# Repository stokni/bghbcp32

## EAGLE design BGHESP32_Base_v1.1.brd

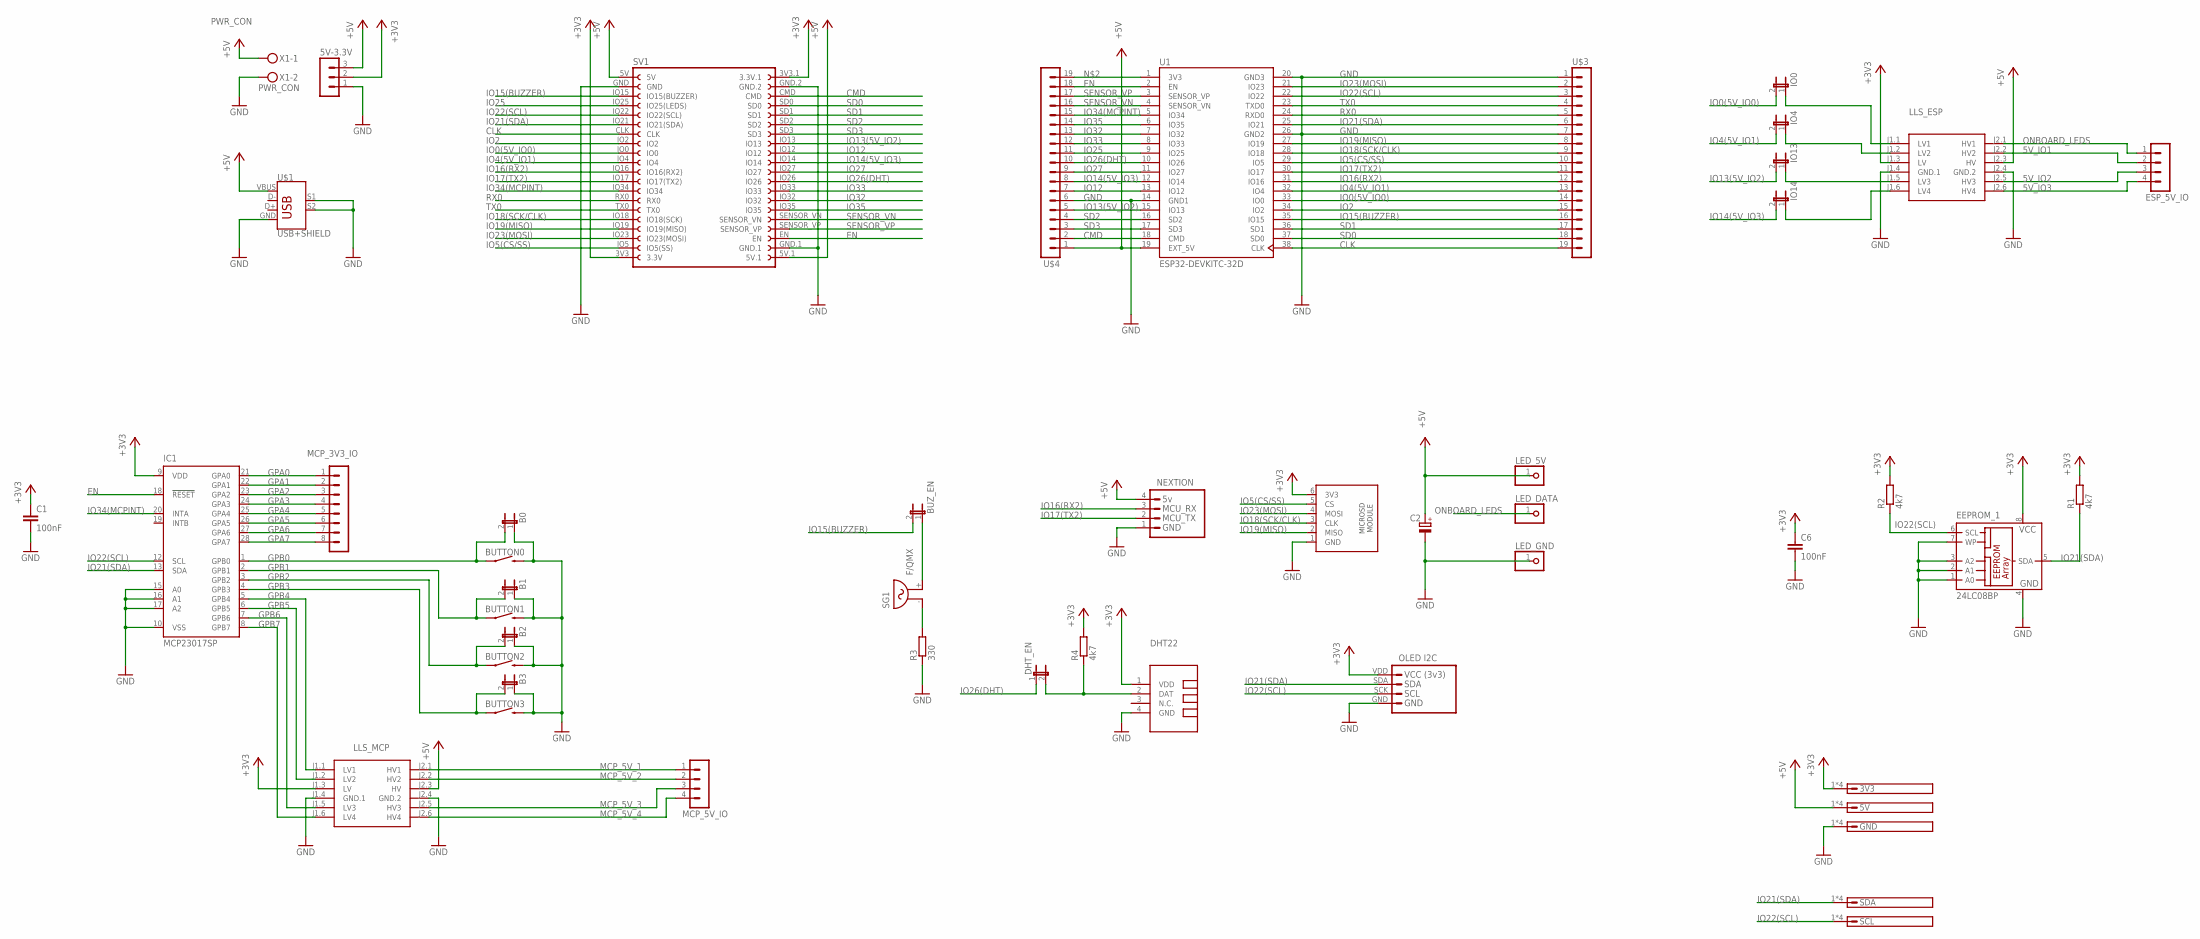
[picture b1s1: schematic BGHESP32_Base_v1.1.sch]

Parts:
3V3, 5V: IO-OUT-4PIO-OUT-4[; IO-OUT-4P
5V-3.3V: MA03-1
B0, B1, B2, B3: JP1E; JP1
BUTTON0, BUTTON1, BUTTON2, BUTTON3: MOMENTARY-SWITCH-SPST-PTH-6.0MM; TACTILE_SWITCH_PTH_6.0MM
BUZ_EN: JP1E; JP1
C1, C6: 100nF; C050-025X075
C2: CPOL-EUE5-10.5; E5-10,5
DHT22: TEMP-HUM-SENSOR-DHT22
DHT_EN: JP1E; JP1
EEPROM_1: 24LC08BP; DIL8
ESP_5V_IO: MA04-1
GND: IO-OUT-4PIO-OUT-4[; IO-OUT-4P
IC1: MCP23017SP; DIL28-3
IO0, IO4, IO13, IO14: JP1E; JP1
LED_5V: PINHD-1X1; 1X01
LED_DATA: PINHD-1X1; 1X01
LED_GND: PINHD-1X1; 1X01
LLS_ESP: LEVEL-SHIFTER-4CH
LLS_MCP: LEVEL-SHIFTER-4CH
MCP_3V3_IO: MA08-1
MCP_5V_IO: MA04-1
R1, R2, R4: 4k7; 0207/10
R3: 330; 0207/10
SCL: IO-OUT-4PIO-OUT-4[; IO-OUT-4P
SDA: IO-OUT-4PIO-OUT-4[; IO-OUT-4P
SG1: F/QMX
SV1: DAUGHTERBOARD_CON
SV3: NEXTION_CON
U1: ESP32-DEVKITC-32D; MODULE_ESP32-DEVKITC-32D
U$1: USB+SHIELD; USB-B-PTH
U$2: I2C_OLED
U$3, U$4: MA19-1
U$5: SDCARD_MODULE
X1: PWR_CON; MKDSN1,5/2-5,08

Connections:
5V_IO1: ESP_5V_IO.2, LLS_ESP.J2.2 (HV2)
5V_IO2: ESP_5V_IO.3, LLS_ESP.J2.5 (HV3)
5V_IO3: ESP_5V_IO.4, LLS_ESP.J2.6 (HV4)
+3V3: 3V3.1, 3V3.2, 3V3.3, 3V3.4, 5V-3.3V.2, C1.1, C6.1, DHT22.1 (VDD), EEPROM_1.8 (VCC), IC1.9 (VDD), LLS_ESP.J1.3 (LV), LLS_MCP.J1.3 (LV), R1.2, R2.2, R4.2, SV1.3V3 (3.3V), SV1.3V3.1 (3.3V.1), U$2.VDD (VCC), U$5.6 (3V3)
+5V: 5V.1, 5V.2, 5V.3, 5V.4, 5V-3.3V.3, C2.+, LED_5V.1, LLS_ESP.J2.3 (HV), LLS_MCP.J2.3 (HV), SV1.5V, SV1.5V.1, SV3.4, U1.19 (EXT_5V), U$1.VBUS, U$4.1, X1.1
CLK: SV1.CLK, U1.38 (CLK), U$3.19
CMD: SV1.CMD, U1.18 (CMD), U$4.2
EN: IC1.18 (!RESET), SV1.EN, U1.2 (EN), U$4.18
GND: 5V-3.3V.1, B0.1, B1.1, B2.1, B3.1, BUTTON0.3 (2), BUTTON1.3 (2), BUTTON2.3 (2), BUTTON3.3 (2), C1.2, C2.-, C6.2, DHT22.4 (GND), EEPROM_1.1 (A0), EEPROM_1.2 (A1), EEPROM_1.3 (A2), EEPROM_1.4 (GND), EEPROM_1.7 (WP), GND.1, GND.2, GND.3, GND.4, IC1.10 (VSS), IC1.15 (A0), IC1.16 (A1), IC1.17 (A2), LED_GND.1, LLS_ESP.J1.4 (GND.1), LLS_ESP.J2.4 (GND.2), LLS_MCP.J1.4 (GND.1), LLS_MCP.J2.4 (GND.2), R3.1, SV1.GND, SV1.GND.1, SV1.GND.2, SV3.1, U1.14 (GND1), U1.20 (GND3), U1.26 (GND2), U$1.GND, U$1.S1, U$1.S2, U$2.GND, U$3.1, U$3.7, U$4.6, U$5.1 (GND), X1.2
GPA0: IC1.21 (GPA0), MCP_3V3_IO.1
GPA1: IC1.22 (GPA1), MCP_3V3_IO.2
GPA2: IC1.23 (GPA2), MCP_3V3_IO.3
GPA3: IC1.24 (GPA3), MCP_3V3_IO.4
GPA4: IC1.25 (GPA4), MCP_3V3_IO.5
GPA5: IC1.26 (GPA5), MCP_3V3_IO.6
GPA6: IC1.27 (GPA6), MCP_3V3_IO.7
GPA7: IC1.28 (GPA7), MCP_3V3_IO.8
GPB0: B0.2, BUTTON0.1, IC1.1 (GPB0)
GPB1: B1.2, BUTTON1.1, IC1.2 (GPB1)
GPB2: B2.2, BUTTON2.1, IC1.3 (GPB2)
GPB3: B3.2, BUTTON3.1, IC1.4 (GPB3)
GPB4: IC1.5 (GPB4), LLS_MCP.J1.1 (LV1)
GPB5: IC1.6 (GPB5), LLS_MCP.J1.2 (LV2)
GPB6: IC1.7 (GPB6), LLS_MCP.J1.5 (LV3)
GPB7: IC1.8 (GPB7), LLS_MCP.J1.6 (LV4)
IO0(5V_IO0): IO0.2, SV1.IO0, U1.33 (IO0), U$3.14
IO2: SV1.IO2, U1.34 (IO2), U$3.15
IO4(5V_IO1): IO4.2, SV1.IO4, U1.32 (IO4), U$3.13
IO5(CS/SS): SV1.IO5 (IO5(SS)), U1.29 (IO5), U$3.10, U$5.5 (CS)
IO12: SV1.IO12, U1.13 (IO12), U$4.7
IO13(5V_IO2): IO13.2, SV1.IO13, U1.15 (IO13), U$4.5
IO14(5V_IO3): IO14.2, SV1.IO14, U1.12 (IO14), U$4.8
IO15(BUZZER): BUZ_EN.2, SV1.IO15 (IO15(BUZZER)), U1.35 (IO15), U$3.16
IO16(RX2): SV1.IO16 (IO16(RX2)), SV3.3, U1.31 (IO16), U$3.12
IO17(TX2): SV1.IO17 (IO17(TX2)), SV3.2, U1.30 (IO17), U$3.11
IO18(SCK/CLK): SV1.IO18 (IO18(SCK)), U1.28 (IO18), U$3.9, U$5.3 (CLK)
IO19(MISO): SV1.IO19 (IO19(MISO)), U1.27 (IO19), U$3.8, U$5.2 (MISO)
IO21(SDA): EEPROM_1.5 (SDA), IC1.13 (SDA), R1.1, SDA.1, SDA.2, SDA.3, SDA.4, SV1.IO21 (IO21(SDA)), U1.25 (IO21), U$2.SDA, U$3.6
IO22(SCL): EEPROM_1.6 (SCL), IC1.12 (SCL), R2.1, SCL.1, SCL.2, SCL.3, SCL.4, SV1.IO22 (IO22(SCL)), U1.22 (IO22), U$2.SCK (SCL), U$3.3
IO23(MOSI): SV1.IO23 (IO23(MOSI)), U1.21 (IO23), U$3.2, U$5.4 (MOSI)
IO25: SV1.IO25 (IO25(LEDS)), U1.9 (IO25), U$4.11
IO26(DHT): DHT_EN.1, SV1.IO26, U1.10 (IO26), U$4.10
IO27: SV1.IO27, U1.11 (IO27), U$4.9
IO32: SV1.IO32, U1.7 (IO32), U$4.13
IO33: SV1.IO33, U1.8 (IO33), U$4.12
IO34(MCPINT): IC1.20 (INTA), SV1.IO34, U1.5 (IO34), U$4.15
IO35: SV1.IO35, U1.6 (IO35), U$4.14
MCP_5V_1: LLS_MCP.J2.1 (HV1), MCP_5V_IO.1
MCP_5V_2: LLS_MCP.J2.2 (HV2), MCP_5V_IO.2
MCP_5V_3: LLS_MCP.J2.5 (HV3), MCP_5V_IO.3
MCP_5V_4: LLS_MCP.J2.6 (HV4), MCP_5V_IO.4
unnamed: R3.2, SG1.- (1)
unnamed: U1.1 (3V3), U$4.19
unnamed: IO0.1, LLS_ESP.J1.1 (LV1)
unnamed: DHT22.2 (DAT), DHT_EN.2, R4.1
unnamed: IO4.1, LLS_ESP.J1.2 (LV2)
unnamed: BUZ_EN.1, SG1.+ (2)
unnamed: IO13.1, LLS_ESP.J1.5 (LV3)
unnamed: IO14.1, LLS_ESP.J1.6 (LV4)
ONBOARD_LEDS: ESP_5V_IO.1, LED_DATA.1, LLS_ESP.J2.1 (HV1)
RX0: SV1.RX0, U1.24 (RXD0), U$3.5
SD0: SV1.SD0, U1.37 (SD0), U$3.18
SD1: SV1.SD1, U1.36 (SD1), U$3.17
SD2: SV1.SD2, U1.16 (SD2), U$4.4
SD3: SV1.SD3, U1.17 (SD3), U$4.3
SENSOR_VN: SV1.SENSOR_VN, U1.4 (SENSOR_VN), U$4.16
SENSOR_VP: SV1.SENSOR_VP, U1.3 (SENSOR_VP), U$4.17
TX0: SV1.TX0, U1.23 (TXD0), U$3.4

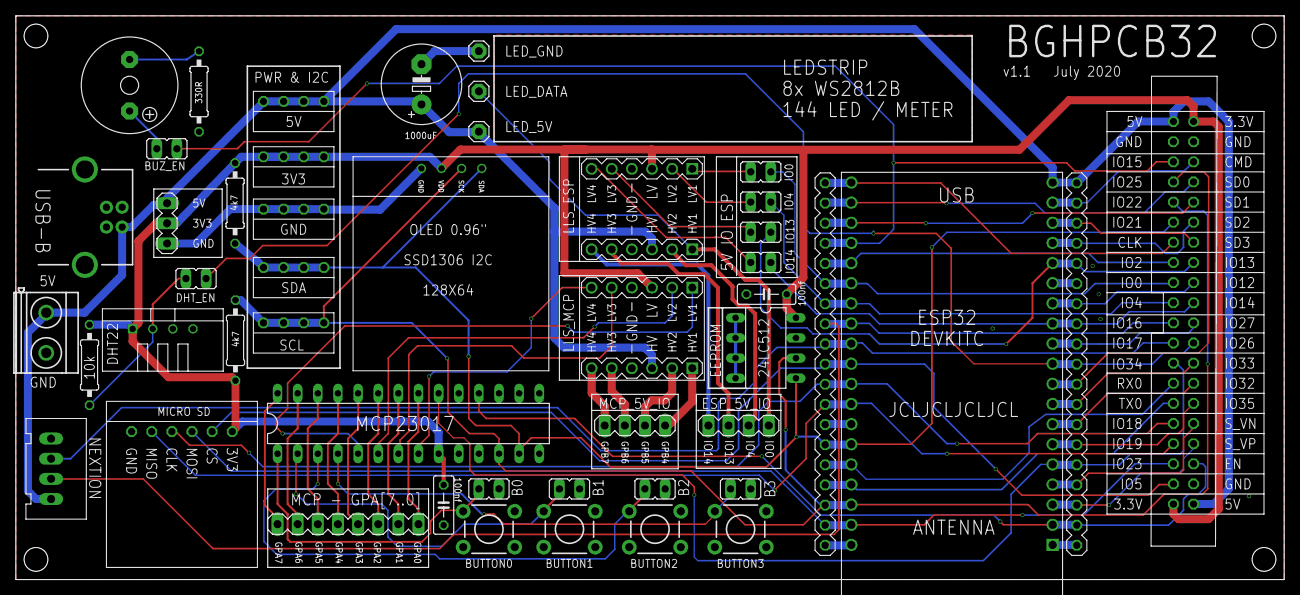
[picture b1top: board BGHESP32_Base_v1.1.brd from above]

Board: 2 copper layers, 160.0 x 71.1 mm, 48 parts (0 on the bottom side), 68 nets.

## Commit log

2020-08-28 Add files via upload
    CAM files for BGHPCB32_v1.1 - just send this file to your favorite PCB shop.

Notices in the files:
parts and their libraries:
SparkFun-Retired: Licensing: Creative Commons ShareAlike 4.0 International - https://creativecommons.org/licenses/by-sa/4.0
diy-modules: Released under the Creative Commons Attribution 4.0 International License: http://creativecommons.org/licenses/by/4.0
